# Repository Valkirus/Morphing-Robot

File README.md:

# Project: Morphex Rotating Arm

This is a WIP project I'm working on. It'll take years to gather knowledge and the budget to actually build it.

## TODO
1. Remodel brackets and servo.
2. Think about materials more.
3. Cost analysis.

## Pictures
Hexapod:

## Costs
**15/12/2024 01:49:**
- $274.51 for All CNC machined parts (so far)
- ~$30 for small hardware pieces (Spacers, Threaded Rods, Bearings,)
- $815.78 for all 33 servos and controllers (with metal horns) 1x HTS-35H, 32x HTD-45H
- $64.18 for brackets to mount each legs
- $72.54 for Custom PCB and Electronics (for now)

**Total:** $1,184.49

## Progress
**15/12/2024 01:48:**
- I have a working model with the original servos. The model is usable and can be visualized.
- Electronics haven't been selected yet but [HiWonder Controller](https://www.hiwonder.com/products/serial-bus-servo-controller) and [HTS-35H Servos](https://www.hiwonder.com/collections/bus-servo/products/hts-35h) are good combos

**15/12/2024 13:30:**
- I have to wait until new years to buy a servo to measure it's dimensions and remodel the servo's CAD model 
- Haven't decided on materials yet, but cnc'ed aluminum for high stress parts and maybe ASA/ABS for the rest

**18/12/2024 13:30:**
- I have remade the model to use HTD-45H servos

**20/12/2024 22:36:**
- Remade a few parts to actually fit read world designs and store bought parts.

**17/01/2025 20:48:**
- Finalized Custom PCB (I think). Ready to be ordered and assembled.

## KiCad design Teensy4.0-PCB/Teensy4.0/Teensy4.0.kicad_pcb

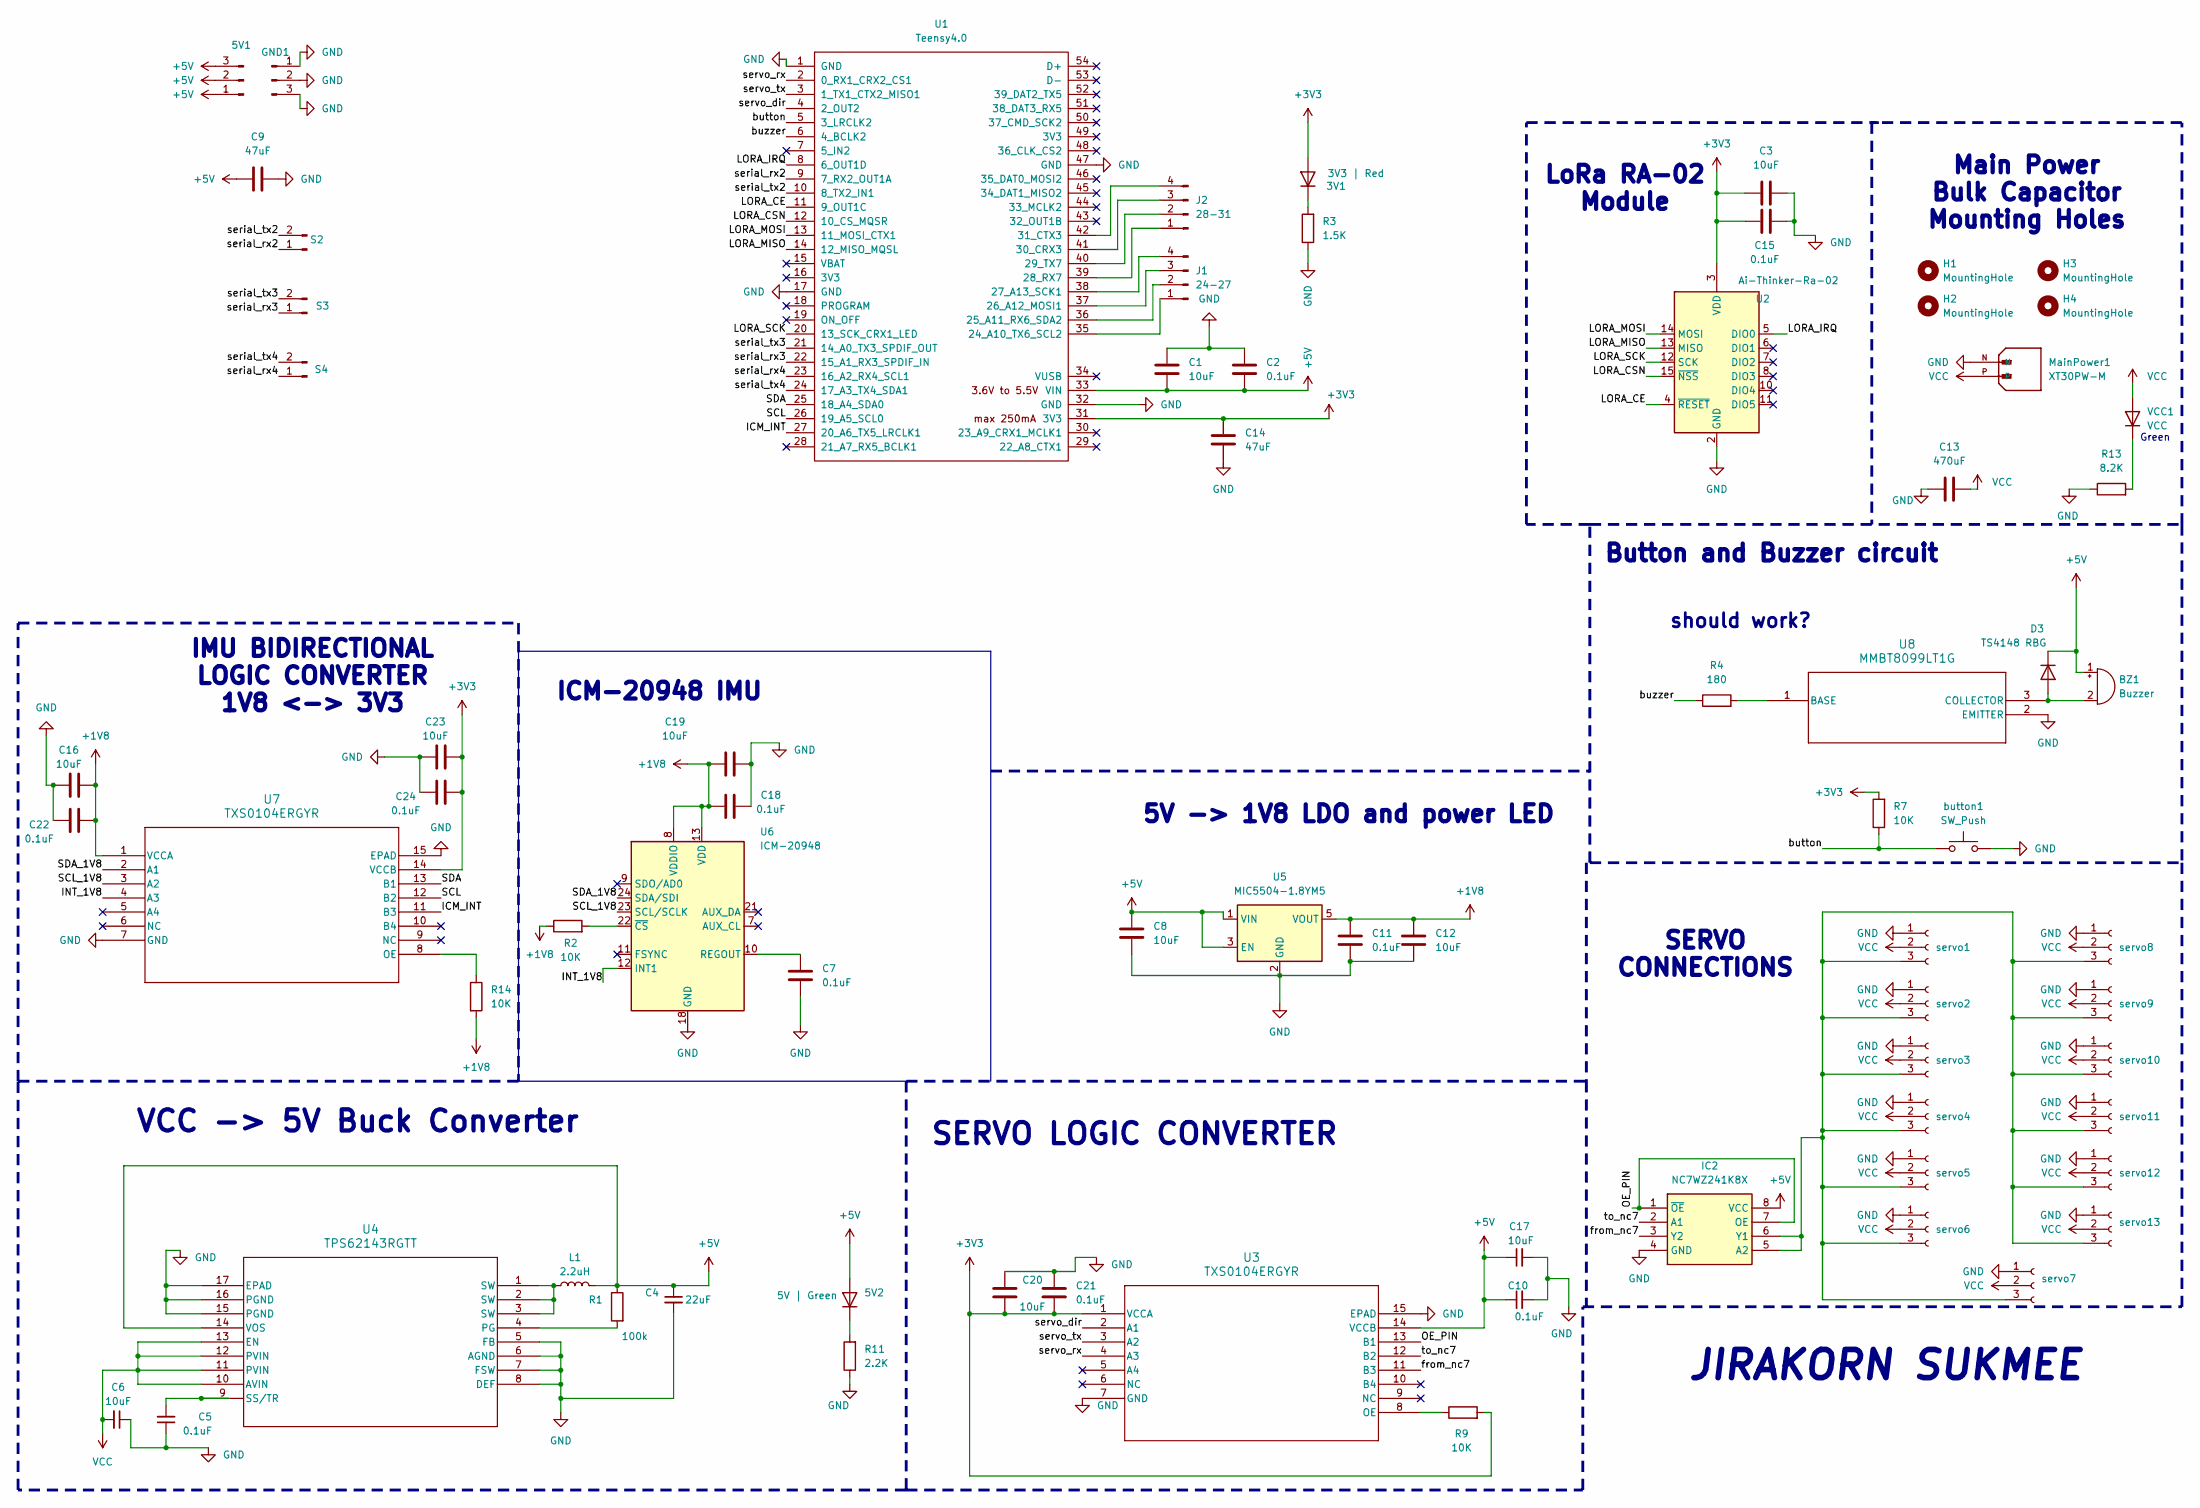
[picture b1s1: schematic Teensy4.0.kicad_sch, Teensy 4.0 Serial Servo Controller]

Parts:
3V1: 3V3 | Red; D_0805_2012Metric_Pad1.15x1.40mm_HandSolder
5V1: Conn_01x03_Pin; PinHeader_1x03_P2.54mm_Vertical
5V2: 5V | Green; D_0805_2012Metric_Pad1.15x1.40mm_HandSolder
BZ1: Buzzer; Buzzer_12x9.5RM7.6
C1, C3, C6, C8, C12, C16, C17, C19, C20, C23: 10uF; C_0805_2012Metric_Pad1.18x1.45mm_HandSolder
C2, C5, C7, C10, C11, C15, C18, C21, C22, C24: 0.1uF; C_0805_2012Metric_Pad1.18x1.45mm_HandSolder
C4: 22uF; C_0805_2012Metric_Pad1.18x1.45mm_HandSolder
C9: 47uF; C_0805_2012Metric_Pad1.18x1.45mm_HandSolder; LCSC C1713
C13: 470uF; CP_Elec_10x10
C14: 47uF; C_0805_2012Metric_Pad1.18x1.45mm_HandSolder
D3: TS4148 RBG; D_0805_2012Metric_Pad1.15x1.40mm_HandSolder
GND1: Conn_01x03_Pin; PinHeader_1x03_P2.54mm_Vertical
H1, H2, H3, H4: MountingHole; MountingHole_3.2mm_M3
IC2: NC7WZ241K8X; SOP50P310X90-8N; Mouser Part Number 512-NC7WZ241K8X
J1: 24-27; PinHeader_1x04_P2.54mm_Vertical
J2: 28-31; PinHeader_1x04_P2.54mm_Vertical
L1: 2.2uH; IND_SRP2512_BRN
MainPower1: XT30PW-M; AMASS_XT30PW-M; PARTREV 1.2
R1: 100k; R_0805_2012Metric_Pad1.20x1.40mm_HandSolder
R2, R7, R9, R14: 10K; R_0805_2012Metric_Pad1.20x1.40mm_HandSolder
R3: 1.5K; R_0805_2012Metric_Pad1.20x1.40mm_HandSolder
R4: 180; R_0805_2012Metric_Pad1.20x1.40mm_HandSolder
R11: 2.2K; R_0805_2012Metric_Pad1.20x1.40mm_HandSolder
R13: 8.2K; R_0805_2012Metric_Pad1.20x1.40mm_HandSolder
S2: CAN_SERIAL3; PinHeader_1x02_P2.54mm_Vertical
S3: SERIAL8; PinHeader_1x02_P2.54mm_Vertical
S4: SERIAL7; PinHeader_1x02_P2.54mm_Vertical
U1: Teensy4.0; Teensy40
U2: Ai-Thinker-Ra-02; Ai-Thinker-Ra-01-LoRa
U3, U7: TXS0104ERGYR; RGY14_2P05X2P05
U4: TPS62143RGTT; RGT16_1P7X1P7
U5: MIC5504-1.8YM5; SOT-23-5
U6: ICM-20948; InvenSense_QFN-24_3x3mm_P0.4mm
U8: MMBT8099LT1G; SOT-23_ONS
VCC1: VCC; D_0805_2012Metric_Pad1.15x1.40mm_HandSolder
button1: SW_Push; SW_SPST_PTS647_Sx38
servo1, servo2, servo3, servo4, servo5, servo6, servo7, servo8, servo9, servo10, servo11, servo12, servo13: Conn_01x03_Socket; JST_PH_B3B-PH-K_1x03_P2.00mm_Vertical

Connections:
+1V8: C11.1, C12.1, C16.2, C18.1, C19.1, C22.1, R2.1, R14.2, U5.5 (VOUT), U6.8 (VDDIO), U6.13 (VDD), U7.1 (VCCA)
+3V3: 3V1.2 (A), C3.1, C14.1, C15.1, C20.2, C21.2, C23.2, C24.1, R7.2, R9.2, U1.31 (3V3), U2.3 (VDD), U3.1 (VCCA), U7.14 (VCCB); also elsewhere on the board
+5V: 5V1.1, 5V1.2, 5V1.3, 5V2.2 (A), BZ1.1 (+), C1.2, C2.2, C4.1, C8.1, C9.1, C10.1, C17.1, D3.1 (K), IC2.8 (VCC), L1.1, R1.1, U1.33 (VIN), U3.14 (VCCB), U4.14 (VOS), U5.1 (VIN), U5.3 (EN); also elsewhere on the board
/ICM_INT: U1.27 (20_A6_TX5_LRCLK1), U7.11 (B3)
/INT_1V8: U6.12 (INT1), U7.4 (A3)
/LORA_CE: U1.11 (9_OUT1C), U2.4 (~RESET)
/LORA_CSN: U1.12 (10_CS_MQSR), U2.15 (~NSS)
/LORA_IRQ: U1.8 (6_OUT1D), U2.5 (DIO0)
/LORA_MISO: U1.14 (12_MISO_MQSL), U2.13 (MISO)
/LORA_MOSI: U1.13 (11_MOSI_CTX1), U2.14 (MOSI)
/LORA_SCK: U1.20 (13_SCK_CRX1_LED), U2.12 (SCK)
/OE_PIN: IC2.1 (~OE), IC2.7 (OE), U3.13 (B1)
/SCL: U1.26 (19_A5_SCL0), U7.12 (B2)
/SCL_1V8: U6.23 (SCL/SCLK), U7.3 (A2)
/SDA: U1.25 (18_A4_SDA0), U7.13 (B1)
/SDA_1V8: U6.24 (SDA/SDI), U7.2 (A1)
/button: R7.1, U1.5 (3_LRCLK2), button1.1; also elsewhere on the board
/buzzer: R4.1, U1.6 (4_BCLK2)
/from_nc7: IC2.3 (Y2), U3.11 (B3)
/serial_rx2: S2.1, U1.9 (7_RX2_OUT1A)
/serial_rx3: S3.1, U1.22 (15_A1_RX3_SPDIF_IN)
/serial_rx4: S4.1, U1.23 (16_A2_RX4_SCL1)
/serial_tx2: S2.2, U1.10 (8_TX2_IN1)
/serial_tx3: S3.2, U1.21 (14_A0_TX3_SPDIF_OUT)
/serial_tx4: S4.2, U1.24 (17_A3_TX4_SDA1)
/servo_dir: U1.4 (2_OUT2), U3.2 (A1)
/servo_rx: U1.2 (0_RX1_CRX2_CS1), U3.4 (A3)
/servo_tx: U1.3 (1_TX1_CTX2_MISO1), U3.3 (A2)
/to_nc7: IC2.2 (A1), U3.12 (B2)
GND: C1.1, C2.1, C3.2, C4.2, C5.1, C6.1, C7.1, C8.2, C9.2, C10.2, C11.2, C12.2, C13.2, C14.2, C15.2, C16.1, C17.2, C18.2, C19.2, C20.1, C21.1, C22.2, C23.1, C24.2, GND1.1, GND1.2, GND1.3, IC2.4 (GND), MainPower1.N, R3.1, R11.1, R13.1, U1.1 (GND), U1.17 (GND), U1.32 (GND), U1.47 (GND), U2.1 (GND), U2.2 (GND), U2.9 (GND), U2.16 (GND), U3.7 (GND), U3.15 (EPAD), U4.5 (FB), U4.6 (AGND), U4.7 (FSW), U4.8 (DEF), U4.15 (PGND), U4.16 (PGND), U4.17 (EPAD), U5.2 (GND), U6.18 (GND), U6.20 (GND), U7.7 (GND), U7.15 (EPAD), U8.2 (EMITTER), button1.2, servo1.1, servo2.1, servo3.1, servo4.1, servo5.1, servo6.1, servo7.1, servo8.1, servo9.1, servo10.1, servo11.1, servo12.1, servo13.1; also elsewhere on the board
unnamed 30: 3V1.1 (K), R3.2; also elsewhere on the board
unnamed 31: 5V2.1 (K), R11.2; also elsewhere on the board
unnamed: BZ1.2 (-), D3.2 (A), U8.3 (COLLECTOR)
unnamed: IC2.5 (A2), IC2.6 (Y1), servo1.3, servo2.3, servo3.3, servo4.3, servo5.3, servo6.3, servo7.3, servo8.3, servo9.3, servo10.3, servo11.3, servo12.3, servo13.3
unnamed: J1.1, U1.35 (24_A10_TX6_SCL2)
unnamed: J1.2, U1.36 (25_A11_RX6_SDA2)
unnamed: J1.3, U1.37 (26_A12_MOSI1)
unnamed: J1.4, U1.38 (27_A13_SCK1)
unnamed: J2.1, U1.39 (28_RX7)
unnamed: J2.2, U1.40 (29_TX7)
unnamed: J2.3, U1.41 (30_CRX3)
unnamed: J2.4, U1.42 (31_CTX3)
unnamed: L1.2, U4.1 (SW), U4.2 (SW), U4.3 (SW)
unnamed: R9.1, U3.8 (OE)
unnamed: R1.2, U4.4 (PG)
unnamed: C5.2, U4.9 (SS/TR)
unnamed: C7.2, U6.10 (REGOUT)
unnamed: R2.2, U6.22 (~CS)
unnamed: R14.1, U7.8 (OE)
unnamed: R4.2, U8.1 (BASE)
unnamed 50: R13.2, VCC1.1 (K); also elsewhere on the board
VCC: C6.2, C13.1, MainPower1.P, U4.10 (AVIN), U4.11 (PVIN), U4.12 (PVIN), U4.13 (EN), VCC1.2 (A), servo1.2, servo2.2, servo3.2, servo4.2, servo5.2, servo6.2, servo7.2, servo8.2, servo9.2, servo10.2, servo11.2, servo12.2, servo13.2; also elsewhere on the board

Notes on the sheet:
VCC -> 5V Buck Converter
JIRAKORN SUKMEE
IMU BIDIRECTIONAL LOGIC CONVERTER 1V8 <-> 3V3
Button and Buzzer circuit
LoRa RA-02 Module
Main Power Bulk Capacitor Mounting Holes
should work?
Green
SERVO CONNECTIONS
ICM-20948 IMU
5V -> 1V8 LDO and power LED
SERVO LOGIC CONVERTER

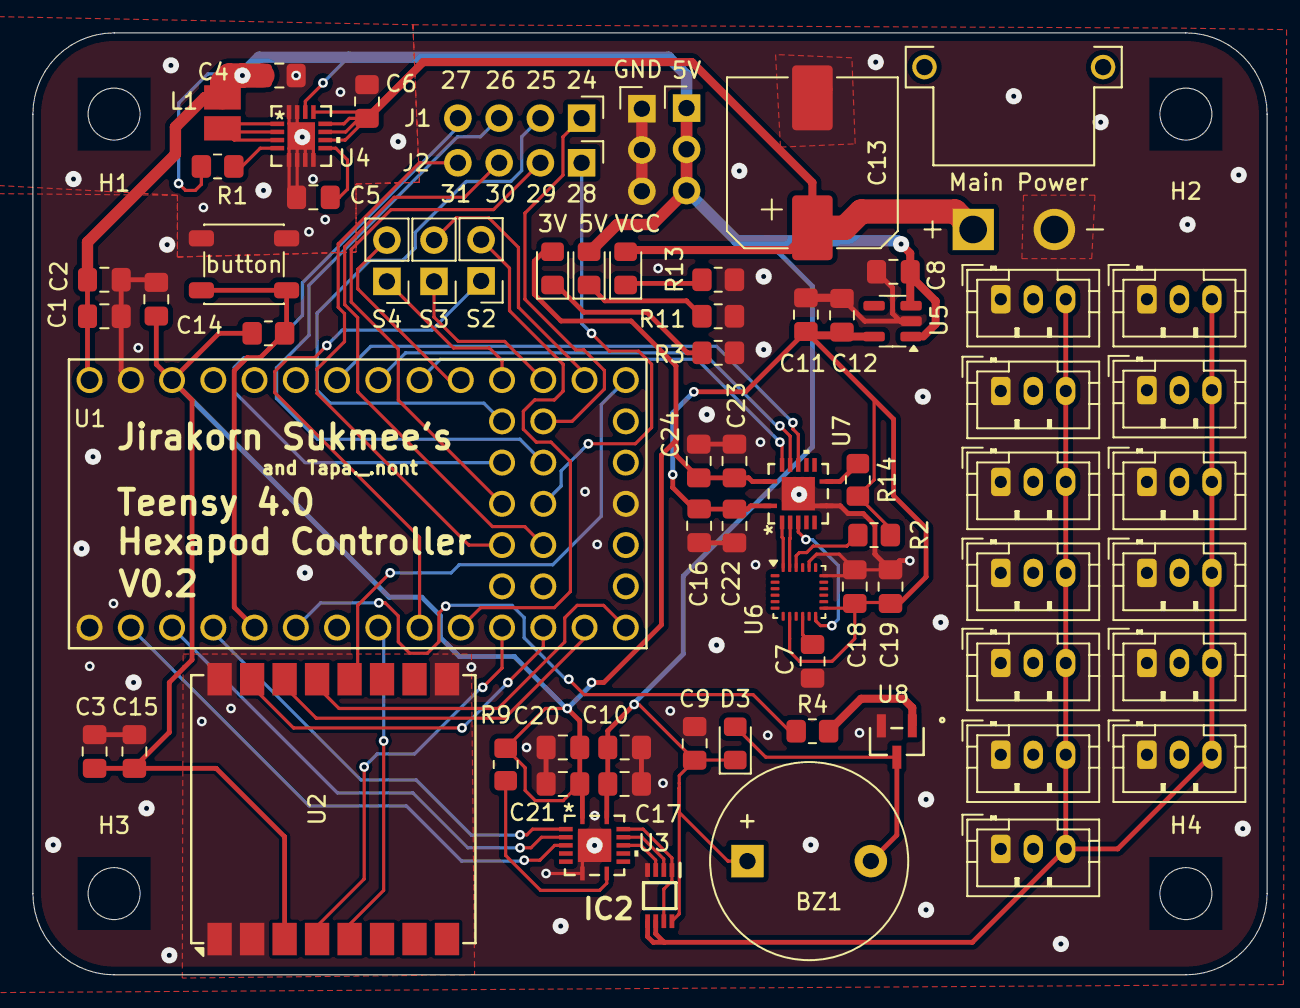
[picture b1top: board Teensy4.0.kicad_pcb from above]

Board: 4 copper layers, 76.0 x 58.0 mm, 74 parts (0 on the bottom side), 52 nets.

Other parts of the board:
3V: 3V3 | Red; D_0805_2012Metric_Pad1.15x1.40mm_HandSolder
5V: 5V | Green; D_0805_2012Metric_Pad1.15x1.40mm_HandSolder
5V#2: Conn_01x03_Pin; PinHeader_1x03_P2.54mm_Vertical
GND: Conn_01x03_Pin; PinHeader_1x03_P2.54mm_Vertical
Main Power: XT30PW-M; AMASS_XT30PW-M
VCC: VCC; D_0805_2012Metric_Pad1.15x1.40mm_HandSolder
button: SW_Push; SW_SPST_PTS647_Sx38

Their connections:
+3V3: 3V.2 (A); also elsewhere on the board
+5V: 5V.2 (A), 5V#2.1, 5V#2.2, 5V#2.3; also elsewhere on the board
/button: button.1; also elsewhere on the board
GND: GND.1, GND.2, GND.3, Main Power.N, button.2; also elsewhere on the board
unnamed 30: 3V.1 (K); also elsewhere on the board
unnamed 31: 5V.1 (K); also elsewhere on the board
unnamed 50: VCC.1 (K); also elsewhere on the board
VCC: Main Power.P, VCC.2 (A); also elsewhere on the board

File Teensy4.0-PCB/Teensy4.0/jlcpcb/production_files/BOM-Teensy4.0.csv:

Comment,Designator,Footprint,LCSC,Quantity
TPS62143RGTT,U4,RGT16_1P7X1P7,C140242,1
TXS0104ERGYR,"U3,U7",RGY14_2P05X2P05,C154926,2
10uF,"C12,C16,C8,C9",C_0805_2012Metric_Pad1.18x1.45mm_HandSolder,C1713,4
100k,R1,R_0805_2012Metric_Pad1.20x1.40mm_HandSolder,C17407,1
10K,"R14,R2,R7,R9",R_0805_2012Metric_Pad1.20x1.40mm_HandSolder,C17414,4
2.2K,R11,R_0805_2012Metric_Pad1.20x1.40mm_HandSolder,C17520,1
8.2K,R13,R_0805_2012Metric_Pad1.20x1.40mm_HandSolder,C17828,1
47uF,C14,C_0805_2012Metric_Pad1.18x1.45mm_HandSolder,C178332,1
Conn_01x03_Socket,"servo1,servo10,servo11,servo12,servo13,servo2,servo3,servo4,servo5,servo6,servo7,servo8,servo9",JST_PH_B3B-PH-K_1x03_P2.00mm_Vertical,C18077745,13
180,R4,R_0805_2012Metric_Pad1.20x1.40mm_HandSolder,C25270,1
470uF,C13,CP_Elec_10x10,C2905295,1
10uF,C6,C_0805_2012Metric_Pad1.18x1.45mm_HandSolder,C40894,1
1.5K,R3,R_0805_2012Metric_Pad1.20x1.40mm_HandSolder,C4310,1
MIC5504-1.8YM5,U5,SOT-23-5,C626116,1
ICM-20948,U6,InvenSense_QFN-24_3x3mm_P0.4mm,C726001,1
22uF,C4,C_0805_2012Metric_Pad1.18x1.45mm_HandSolder,C76637,1
10uF,"C1,C17,C23,C3",C_0805_2012Metric_Pad1.18x1.45mm_HandSolder,C77075,4
0.1uF,"C10,C11,C15,C18,C2,C21,C22,C24,C5,C7",C_0805_2012Metric_Pad1.18x1.45mm_HandSolder,C86041,10
10uF,"C19,C20",C_0805_2012Metric_Pad1.18x1.45mm_HandSolder,C87157,2
2.2uH,L1,IND_SRP2512_BRN,C913212,1
Buzzer,BZ1,Buzzer_12x9.5RM7.6,C96078,1
NC7WZ241K8X,IC2,SOP50P310X90-8N,,1
24-27,J1,PinHeader_1x04_P2.54mm_Vertical,,1
Ai-Thinker-Ra-02,U2,Ai-Thinker-Ra-01-LoRa,,1
SERIAL7,S4,PinHeader_1x02_P2.54mm_Vertical,,1
CAN_SERIAL3,S2,PinHeader_1x02_P2.54mm_Vertical,,1
Teensy4.0,U1,Teensy40,,1
28-31,J2,PinHeader_1x04_P2.54mm_Vertical,,1
SERIAL8,S3,PinHeader_1x02_P2.54mm_Vertical,,1
TS4148 RBG,D3,D_0805_2012Metric_Pad1.15x1.40mm_HandSolder,,1
MMBT8099LT1G,U8,SOT-23_ONS,,1

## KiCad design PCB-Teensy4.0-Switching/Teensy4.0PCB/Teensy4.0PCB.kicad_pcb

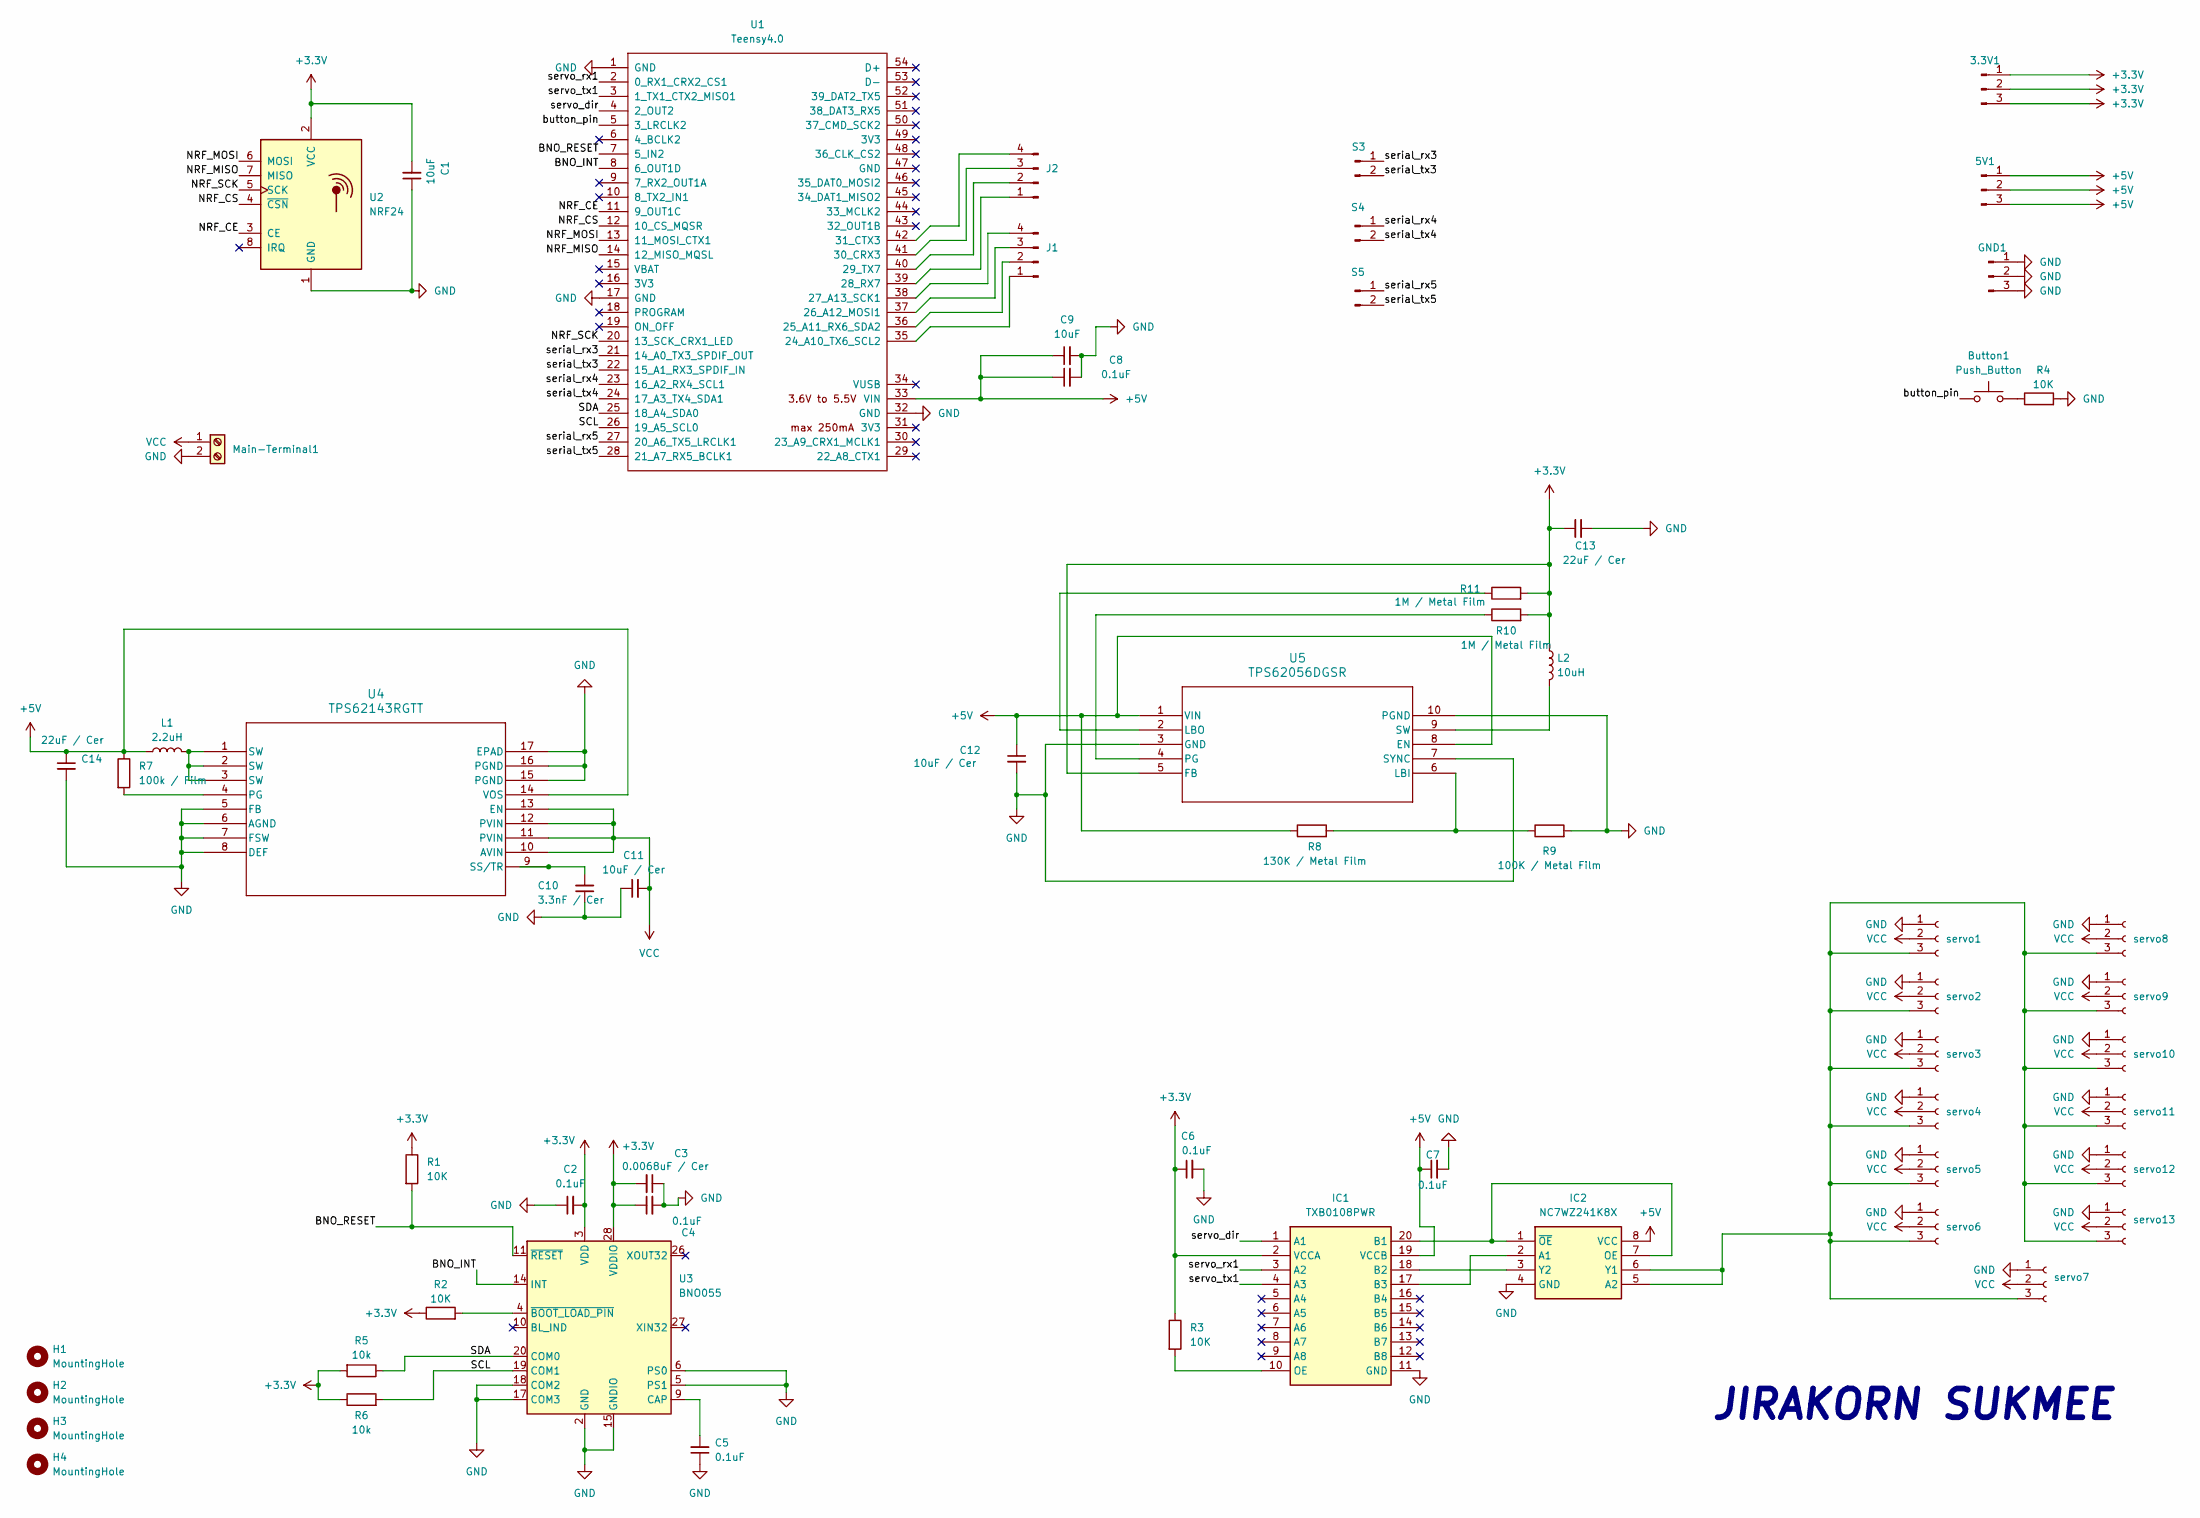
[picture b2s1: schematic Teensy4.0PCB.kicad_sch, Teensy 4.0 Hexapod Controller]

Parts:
3.3V1, 5V1: Conn_01x03_Pin; PinHeader_1x03_P2.54mm_Vertical
Button1: Push_Button; SW_PUSH_6mm
C1: 10uF; C_1206_3216Metric_Pad1.33x1.80mm_HandSolder
C2, C4, C7, C8: 0.1uF; C_0402_1005Metric_Pad0.74x0.62mm_HandSolder
C3: 0.0068uF / Cer; C_0402_1005Metric_Pad0.74x0.62mm_HandSolder
C5: 0.1uF; C_1206_3216Metric_Pad1.33x1.80mm_HandSolder
C6: 0.1uF; C_0805_2012Metric_Pad1.18x1.45mm_HandSolder
C9: 10uF; C_0402_1005Metric_Pad0.74x0.62mm_HandSolder
C10: 3.3nF / Cer; C_0402_1005Metric_Pad0.74x0.62mm_HandSolder
C11, C12: 10uF / Cer; C_0402_1005Metric_Pad0.74x0.62mm_HandSolder
C13, C14: 22uF / Cer; C_0402_1005Metric_Pad0.74x0.62mm_HandSolder
GND1: Conn_01x03_Pin; PinHeader_1x03_P2.54mm_Vertical
H1, H2, H3, H4: MountingHole; MountingHole_3.2mm_M3
IC1: TXB0108PWR; SOP65P640X120-20N; Mouser Part Number 595-TXB0108PWR
IC2: NC7WZ241K8X; SOP50P310X90-8N; Mouser Part Number 512-NC7WZ241K8X
J1, J2: Conn_01x04_Pin; PinHeader_1x04_P2.54mm_Vertical
L1: 2.2uH; IND_SRP2512_BRN
L2: 10uH; L_Coilcraft_XxL4030
Main-Terminal1: Main Terminal; TerminalBlock_Phoenix_MKDS-1,5-2-5.08_1x02_P5.08mm_Horizont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
R1, R2, R3: 10K; R_1206_3216Metric_Pad1.30x1.75mm_HandSolder
R4: 10K; R_0402_1005Metric_Pad0.72x0.64mm_HandSolder
R5, R6: 10k; R_0402_1005Metric_Pad0.72x0.64mm_HandSolder
R7: 100k / Film; R_0402_1005Metric_Pad0.72x0.64mm_HandSolder
R8: 130K / Metal Film; R_0402_1005Metric_Pad0.72x0.64mm_HandSolder
R9: 100K / Metal Film; R_0402_1005Metric_Pad0.72x0.64mm_HandSolder
R10, R11: 1M / Metal Film; R_0603_1608Metric_Pad0.98x0.95mm_HandSolder
S3: SERIAL7; PinHeader_1x02_P2.54mm_Vertical
S4: SERIAL8; PinHeader_1x02_P2.54mm_Vertical
S5: CAN_SERIAL3; PinHeader_1x02_P2.54mm_Vertical
U1: Teensy4.0; Teensy40_SMT
U2: NRF24; nRF24L01_Breakout
U3: BNO055; LGA-28_5.2x3.8mm_P0.5mm
U4: TPS62143RGTT; RGT16_1P7X1P7
U5: TPS62056DGSR; DGS10
servo1, servo2, servo3, servo4, servo5, servo6, servo7, servo8, servo9, servo10, servo11, servo12, servo13: Conn_01x03_Socket; JST_PH_B3B-PH-K_1x03_P2.00mm_Vertical

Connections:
+3.3V: 3.3V1.1, 3.3V1.2, 3.3V1.3, C1.2, C2.2, C3.2, C4.1, C6.1, C13.1, IC1.2 (VCCA), L2.1, R1.1, R2.1, R3.1, R5.2, R6.1, R10.2, R11.2, U2.2 (VCC), U3.3 (VDD), U3.28 (VDDIO), U5.5 (FB)
+5V: 5V1.1, 5V1.2, 5V1.3, C7.1, C8.1, C9.1, C12.1, C14.1, IC1.19 (VCCB), IC2.8 (VCC), L1.1, R7.1, R8.1, U1.33 (VIN), U4.14 (VOS), U5.1 (VIN), U5.8 (EN)
/BNO_INT: U1.8 (6_OUT1D), U3.14 (INT)
/BNO_RESET: R1.2, U1.7 (5_IN2), U3.11 (~RESET)
/NRF_CE: U1.11 (9_OUT1C), U2.3 (CE)
/NRF_CS: U1.12 (10_CS_MQSR), U2.4 (~CSN)
/NRF_MISO: U1.14 (12_MISO_MQSL), U2.7 (MISO)
/NRF_MOSI: U1.13 (11_MOSI_CTX1), U2.6 (MOSI)
/NRF_SCK: U1.20 (13_SCK_CRX1_LED), U2.5 (SCK)
/SCL: R6.2, U1.26 (19_A5_SCL0), U3.19 (COM1)
/SDA: R5.1, U1.25 (18_A4_SDA0), U3.20 (COM0)
/button_pin: Button1.1, U1.5 (3_LRCLK2); also elsewhere on the board
/serial_rx3: S3.1, U1.21 (14_A0_TX3_SPDIF_OUT)
/serial_rx4: S4.1, U1.23 (16_A2_RX4_SCL1)
/serial_rx5: S5.1, U1.27 (20_A6_TX5_LRCLK1)
/serial_tx3: S3.2, U1.22 (15_A1_RX3_SPDIF_IN)
/serial_tx4: S4.2, U1.24 (17_A3_TX4_SDA1)
/serial_tx5: S5.2, U1.28 (21_A7_RX5_BCLK1)
/servo_dir: IC1.1 (A1), U1.4 (2_OUT2)
/servo_rx1: IC1.3 (A2), U1.2 (0_RX1_CRX2_CS1)
/servo_tx1: IC1.4 (A3), U1.3 (1_TX1_CTX2_MISO1)
GND: C1.1, C2.1, C3.1, C4.2, C5.1, C6.2, C7.2, C8.2, C9.2, C10.1, C11.1, C12.2, C13.2, C14.2, GND1.1, GND1.2, GND1.3, IC1.11 (GND), IC2.4 (GND), Main-Terminal1.2, R4.2, R9.2, U1.1 (GND), U1.17 (GND), U1.32 (GND), U2.1 (GND), U3.2 (GND), U3.5 (PS1), U3.6 (PS0), U3.15 (GNDIO), U3.16 (GNDIO), U3.17 (COM3), U3.18 (COM2), U3.25 (GNDIO), U4.5 (FB), U4.6 (AGND), U4.7 (FSW), U4.8 (DEF), U4.15 (PGND), U4.16 (PGND), U4.17 (EPAD), U5.3 (GND), U5.7 (SYNC), U5.10 (PGND), servo1.1, servo2.1, servo3.1, servo4.1, servo5.1, servo6.1, servo7.1, servo8.1, servo9.1, servo10.1, servo11.1, servo12.1, servo13.1
unnamed 22: Button1.2, R4.1; also elsewhere on the board
unnamed: IC1.20 (B1), IC2.1 (~OE), IC2.7 (OE)
unnamed: IC1.18 (B2), IC2.3 (Y2)
unnamed: IC1.17 (B3), IC2.2 (A1)
unnamed: IC1.10 (OE), R3.2
unnamed: IC2.5 (A2), IC2.6 (Y1), servo1.3, servo2.3, servo3.3, servo4.3, servo5.3, servo6.3, servo7.3, servo8.3, servo9.3, servo10.3, servo11.3, servo12.3, servo13.3
unnamed: J1.1, U1.35 (24_A10_TX6_SCL2)
unnamed: J1.2, U1.36 (25_A11_RX6_SDA2)
unnamed: J1.3, U1.37 (26_A12_MOSI1)
unnamed: J1.4, U1.38 (27_A13_SCK1)
unnamed: J2.1, U1.39 (28_RX7)
unnamed: J2.2, U1.40 (29_TX7)
unnamed: J2.3, U1.41 (30_CRX3)
unnamed: J2.4, U1.42 (31_CTX3)
unnamed: L1.2, U4.1 (SW), U4.2 (SW), U4.3 (SW)
unnamed: C5.2, U3.9 (CAP)
unnamed: R2.2, U3.4 (~BOOT_LOAD_PIN)
unnamed: R7.2, U4.4 (PG)
unnamed: C10.2, U4.9 (SS/TR)
unnamed: R8.2, R9.1, U5.6 (LBI)
unnamed: R11.1, U5.2 (LBO)
unnamed: R10.1, U5.4 (PG)
unnamed: L2.2, U5.9 (SW)
VCC: C11.2, Main-Terminal1.1, U4.10 (AVIN), U4.11 (PVIN), U4.12 (PVIN), U4.13 (EN), servo1.2, servo2.2, servo3.2, servo4.2, servo5.2, servo6.2, servo7.2, servo8.2, servo9.2, servo10.2, servo11.2, servo12.2, servo13.2

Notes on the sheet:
JIRAKORN SUKMEE

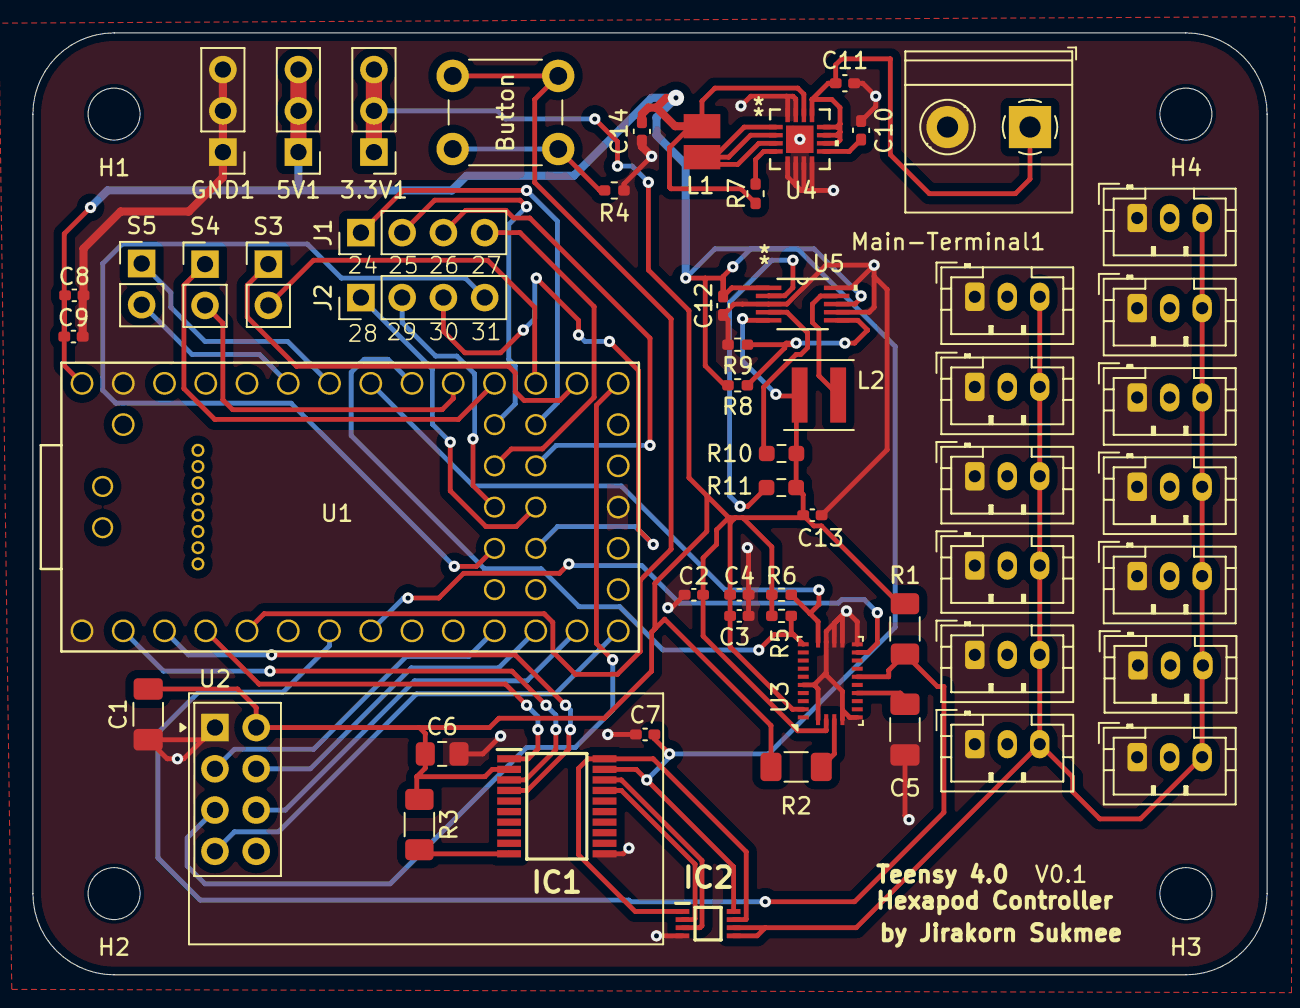
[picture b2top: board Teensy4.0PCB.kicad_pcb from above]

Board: 4 copper layers, 76.0 x 58.0 mm, 61 parts (0 on the bottom side), 46 nets.

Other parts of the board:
Button: Push_Button; SW_PUSH_6mm

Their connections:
/button_pin: Button.1; also elsewhere on the board
unnamed 22: Button.2; also elsewhere on the board
